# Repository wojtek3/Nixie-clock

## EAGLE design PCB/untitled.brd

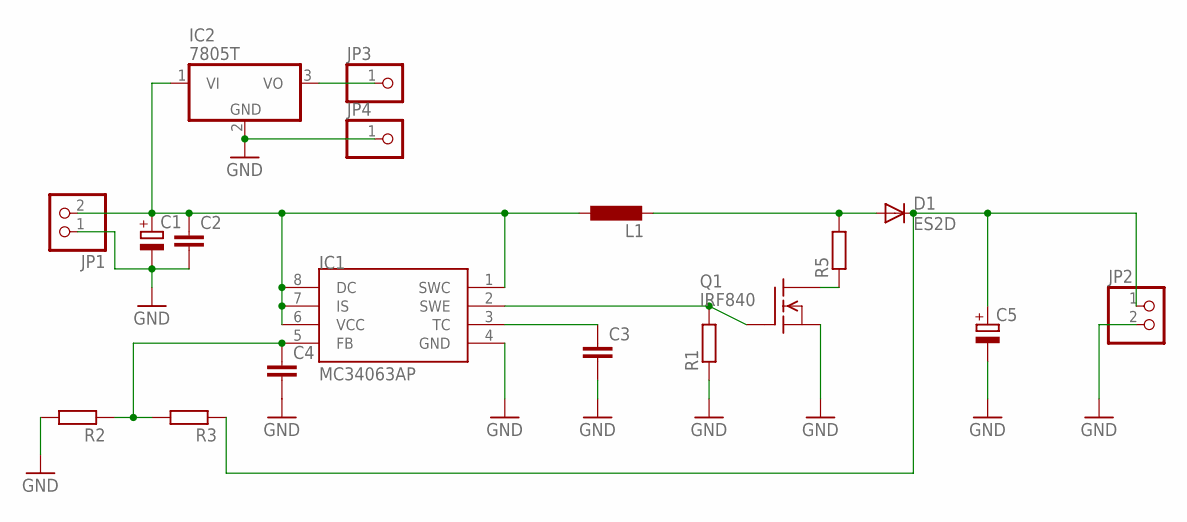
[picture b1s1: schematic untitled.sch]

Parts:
C1, C5: CPOL-EUE3.5-8; E3,5-8
C2, C3, C4: C-EU050-025X075; C050-025X075
D1: ES2D; SMB
IC1: MC34063AP; DIL08
IC2: 7805T; TO220H
JP1, JP2: PINHD-1X2; 1X02
JP3, JP4: PINHD-1X1; 1X01
L1: L-EUTJ3-U1; TJ3-U1
Q1: IRF840; TO220
R1, R2, R3: R-EU_0207/7; 0207/7
R5: R-EU_0207/15; 0207/15

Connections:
GND: C1.-, C2.2, C3.2, C4.2, C5.-, IC1.4 (GND), IC2.2 (GND), JP1.1, JP2.2, JP4.1, Q1.3 (S), R1.1, R2.2
unnamed: C1.+, C2.1, IC1.1 (SWC), IC1.6 (VCC), IC1.7 (IS), IC1.8 (DC), IC2.1 (VI), JP1.2, L1.1
unnamed: C4.1, IC1.5 (FB), R2.1, R3.2
unnamed: C3.1, IC1.3 (TC)
unnamed: D1.A, L1.2, R5.2
unnamed: IC1.2 (SWE), Q1.1 (G), R1.2
unnamed: Q1.2 (D), R5.1
unnamed: C5.+, D1.C, JP2.1, R3.1
unnamed: IC2.3 (VO), JP3.1

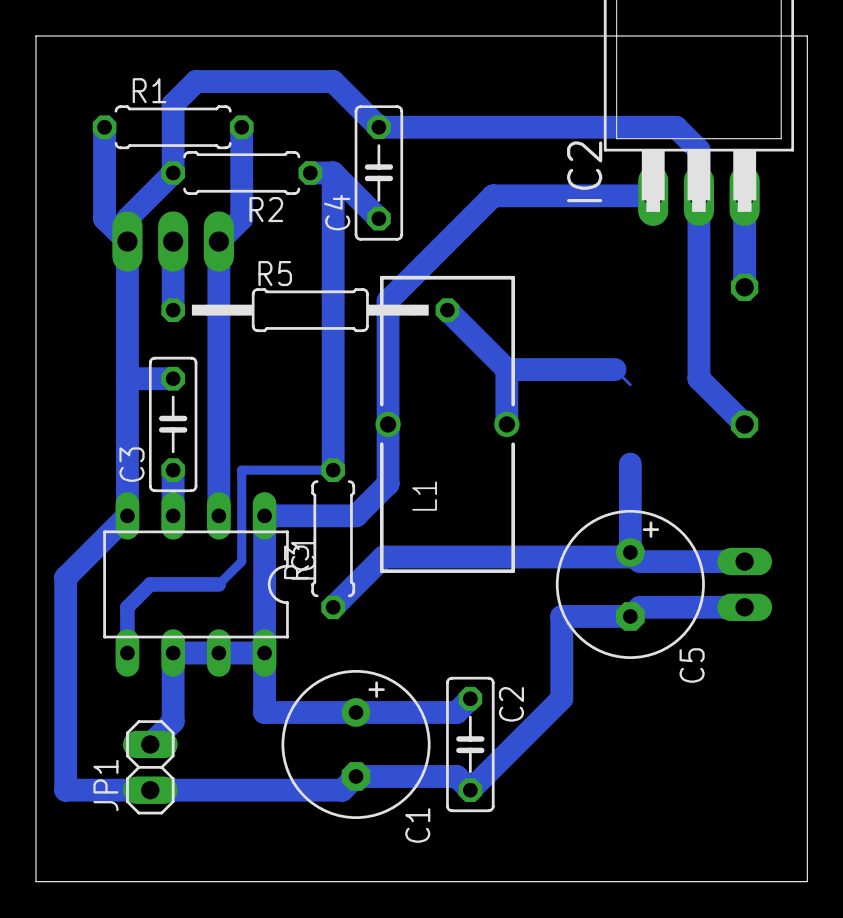
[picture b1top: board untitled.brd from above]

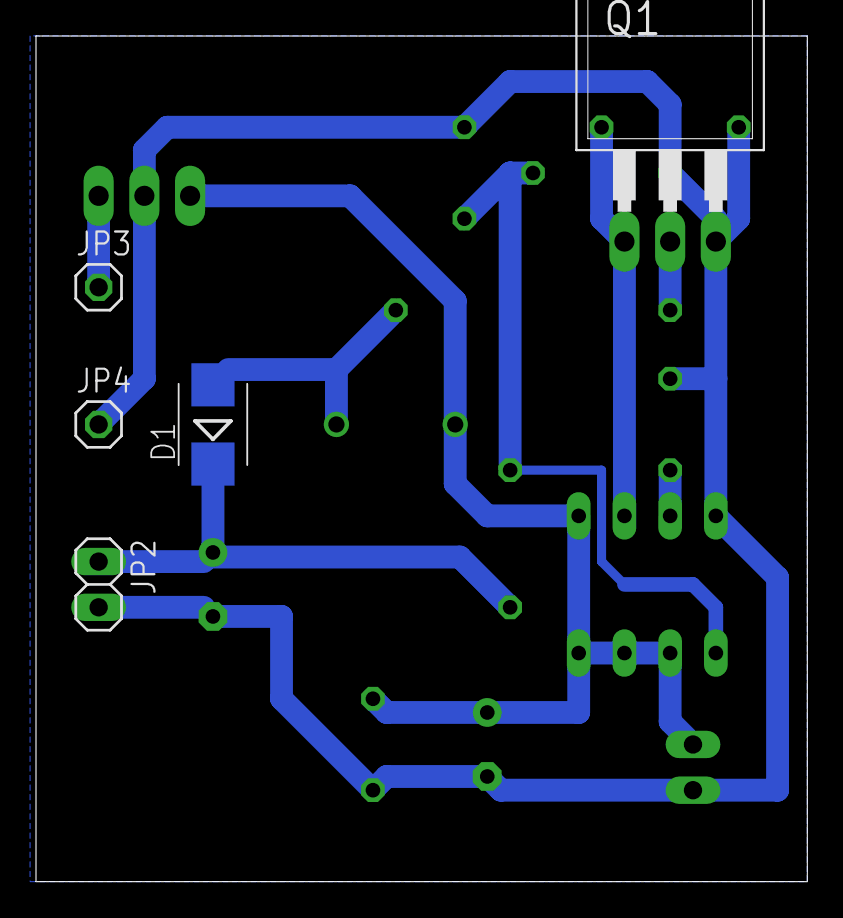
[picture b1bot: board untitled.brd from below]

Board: 2 copper layers, 42.9 x 47.0 mm, 18 parts (5 on the bottom side), 9 nets.

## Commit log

2020-03-17 Rename testy_rtc.ino to Nixie_DS1307_v1.0.ino
2020-03-17 Create PCB
2020-03-17 Rename Nixie_DS1307_v1.0.ino to code/Nixie_DS1307_v1.0.ino
2020-03-17 Rename code/Nixie_DS1307_v1.0.ino to Code/Nixie_DS1307_v1.0.ino
2020-03-17 Rename untitled.brd to Motherboard.brd
2020-03-17 Rename untitled.sch to Motherboard.sch
2020-03-17 Rename untitled.brd to Power.brd
